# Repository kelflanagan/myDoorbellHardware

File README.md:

# myDoorbell
Software, Schematics, PCB designs, and other material for the myDoorbell project

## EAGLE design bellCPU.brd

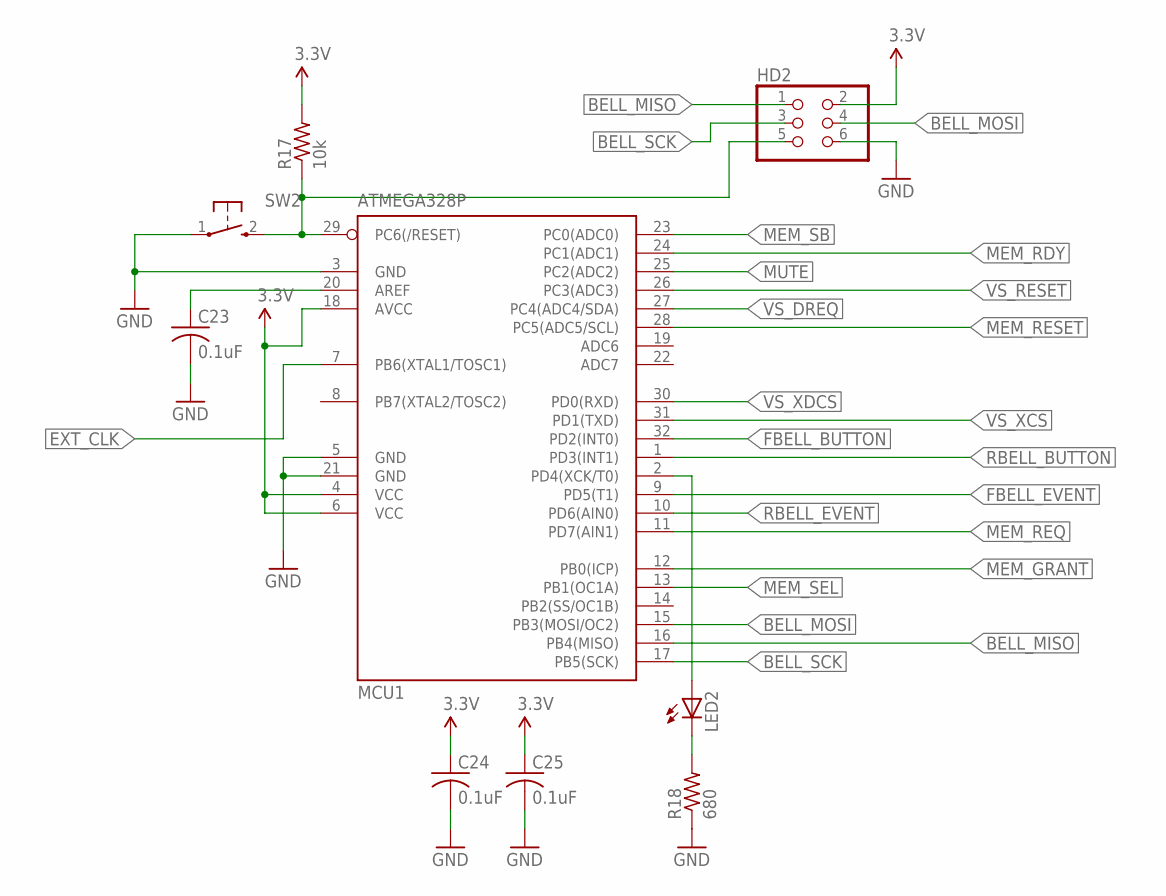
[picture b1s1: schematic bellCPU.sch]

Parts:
C23, C24, C25: 0.1uF; 0603_CAP; DIGIKEY# 399-1096-1-ND
HD2: HEADER_2X3
LED2: LED0603; 0603_LED
MCU1: ATMEGA328P; TQFP32-08
R17: 10k; 0603_RESISTOR; DIGIKEY# P10KGCT-ND
R18: 680; 0603_RESISTOR; DIGIKEY# P680GCT-ND
SW2: SWITCH; SWITCH_TAC

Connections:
3.3V: C24.1, C25.1, HD2.2, MCU1.4 (VCC), MCU1.6 (VCC), MCU1.18 (AVCC), R17.2
BELL_MISO: HD2.1, MCU1.16 (PB4(MISO))
BELL_MOSI: HD2.4, MCU1.15 (PB3(MOSI/OC2))
BELL_RESET: HD2.5, MCU1.29 (PC6(/RESET)), R17.1, SW2.2
BELL_SCK: HD2.3, MCU1.17 (PB5(SCK))
EXT_CLK: MCU1.7 (PB6(XTAL1/TOSC1))
FBELL_BUTTON: MCU1.32 (PD2(INT0))
FBELL_EVENT: MCU1.9 (PD5(T1))
GND: C23.2, C24.2, C25.2, HD2.6, MCU1.3 (GND), MCU1.5 (GND), MCU1.21 (GND), R18.1, SW2.1
MEM_GRANT: MCU1.12 (PB0(ICP))
MEM_RDY: MCU1.24 (PC1(ADC1))
MEM_REQ: MCU1.11 (PD7(AIN1))
MEM_RESET: MCU1.28 (PC5(ADC5/SCL))
MEM_SB: MCU1.23 (PC0(ADC0))
MEM_SEL: MCU1.13 (PB1(OC1A))
MUTE: MCU1.25 (PC2(ADC2))
unnamed: C23.1, MCU1.20 (AREF)
unnamed: LED2.C, R18.2
unnamed: LED2.A, MCU1.2 (PD4(XCK/T0))
RBELL_BUTTON: MCU1.1 (PD3(INT1))
RBELL_EVENT: MCU1.10 (PD6(AIN0))
VS_DREQ: MCU1.27 (PC4(ADC4/SDA))
VS_RESET: MCU1.26 (PC3(ADC3))
VS_XCS: MCU1.31 (PD1(TXD))
VS_XDCS: MCU1.30 (PD0(RXD))

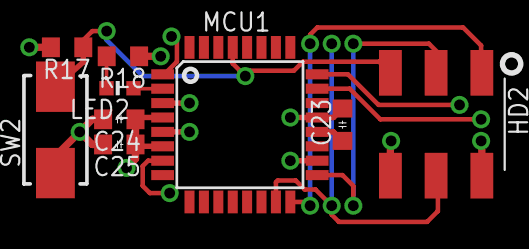
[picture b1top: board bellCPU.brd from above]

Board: 4 copper layers, 9 parts (0 on the bottom side), 9 nets.

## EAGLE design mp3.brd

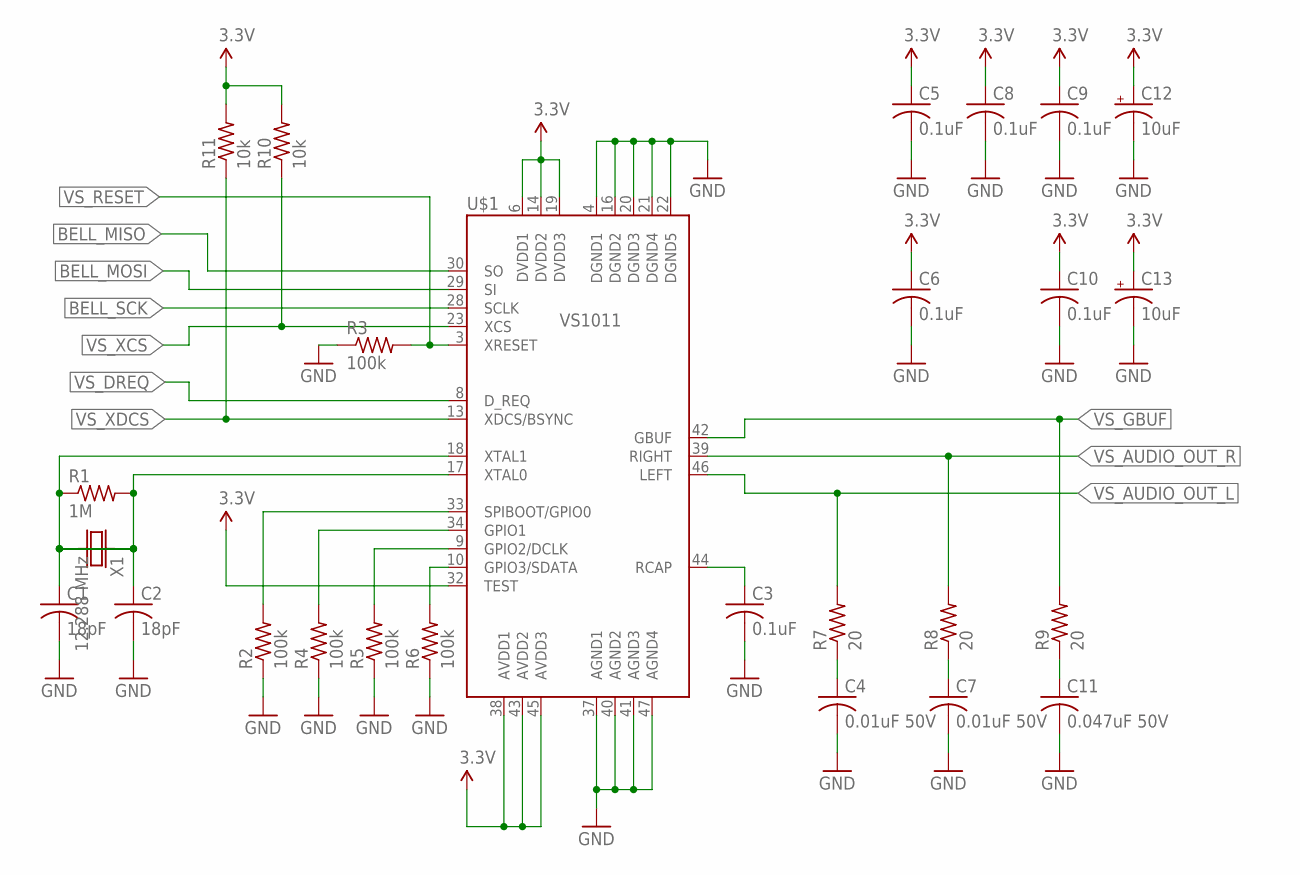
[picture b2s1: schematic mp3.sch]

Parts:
C1, C2: 18pF; 0603_CAP; DIGIKEY# 445-1272-1-ND
C3, C5, C6, C8, C9, C10: 0.1uF; 0603_CAP; DIGIKEY# 399-1096-1-ND
C4, C7: 0.01uF 50V; 0603_CAP; DIGIKEY# 445-1311-1-ND
C11: 0.047uF 50V; 0603_CAP; DIGIKEY# 445-1313-1-ND
C12, C13: 10uF; B_CAP; DIGIKEY# PCE3782CT-ND
R1: 1M; 0603_RESISTOR; DIGIKEY# 311-1.0MGRCT-ND
R2, R3, R4, R5, R6: 100k; 0603_RESISTOR; DIGIKEY# 311-100KGRCT-ND
R7, R8, R9: 20; 0603_RESISTOR; DIGIKEY# 311-20GRCT-ND
R10, R11: 10k; 0603_RESISTOR; DIGIKEY# 311-100KGRCT-ND
U$1: VS1011; LQFP-48
X1: 12.288 MHz; CRYSTAL_5X3; DIGIKEY# 887-1082-1-ND

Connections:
3.3V: C5.1, C6.1, C8.1, C9.1, C10.1, C12.+, C13.+, R10.2, R11.2, U$1.6 (DVDD1), U$1.14 (DVDD2), U$1.19 (DVDD3), U$1.32 (TEST), U$1.38 (AVDD1), U$1.43 (AVDD2), U$1.45 (AVDD3)
BELL_MISO: U$1.30 (SO)
BELL_MOSI: U$1.29 (SI)
BELL_SCK: U$1.28 (SCLK)
GND: C1.2, C2.2, C3.2, C4.2, C5.2, C6.2, C7.2, C8.2, C9.2, C10.2, C11.2, C12.-, C13.-, R2.1, R3.1, R4.1, R5.1, R6.1, U$1.4 (DGND1), U$1.16 (DGND2), U$1.20 (DGND3), U$1.21 (DGND4), U$1.22 (DGND5), U$1.37 (AGND1), U$1.40 (AGND2), U$1.41 (AGND3), U$1.47 (AGND4)
unnamed: C1.1, R1.1, U$1.18 (XTAL1), X1.1
unnamed: C2.1, R1.2, U$1.17 (XTAL0), X1.2
unnamed: C3.1, U$1.44 (RCAP)
unnamed: R6.2, U$1.10 (GPIO3/SDATA)
unnamed: R5.2, U$1.9 (GPIO2/DCLK)
unnamed: R4.2, U$1.34 (GPIO1)
unnamed: R2.2, U$1.33 (SPIBOOT/GPIO0)
unnamed: C4.1, R7.1
unnamed: C7.1, R8.1
unnamed: C11.1, R9.1
VS_AUDIO_OUT_L: R7.2, U$1.46 (LEFT)
VS_AUDIO_OUT_R: R8.2, U$1.39 (RIGHT)
VS_DREQ: U$1.8 (D_REQ)
VS_GBUF: R9.2, U$1.42 (GBUF)
VS_RESET: R3.2, U$1.3 (XRESET)
VS_XCS: R10.1, U$1.23 (XCS)
VS_XDCS: R11.1, U$1.13 (XDCS/BSYNC)

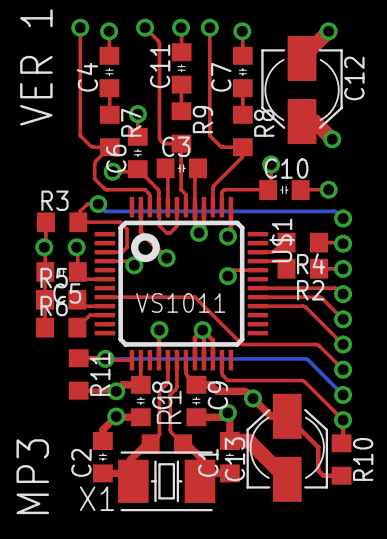
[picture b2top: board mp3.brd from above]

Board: 4 copper layers, 26 parts (0 on the bottom side), 18 nets.

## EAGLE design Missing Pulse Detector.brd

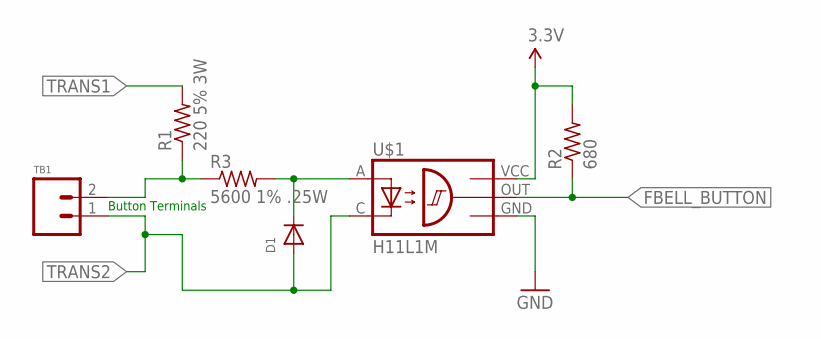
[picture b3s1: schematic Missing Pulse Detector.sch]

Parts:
D1: DIODE0603; 0603_DIODE; DIGIKEY# 641-1002-1-ND
R1: 220 5% 3W; 4122_RESISTOR; DIGIKEY# A103620CT-ND
R2: 680; 0603_RESISTOR; DIGIKEY# P680GCT-ND
R3: 5600 1% .25W; 1206_RESISTOR; DIGIKEY# P5.60KFCT-ND
TB1: TERMINAL_BLOCK_2
U$1: H11L1M; SOIC6

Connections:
3.3V: R2.2, U$1.VCC
FBELL_BUTTON: R2.1, U$1.OUT
FDB1: R1.1, R3.1, TB1.2
GND: U$1.GND
unnamed: D1.C, R3.2, U$1.A
TRANS1: R1.2
TRANS2: D1.A, TB1.1, U$1.C

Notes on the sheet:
Button Terminals

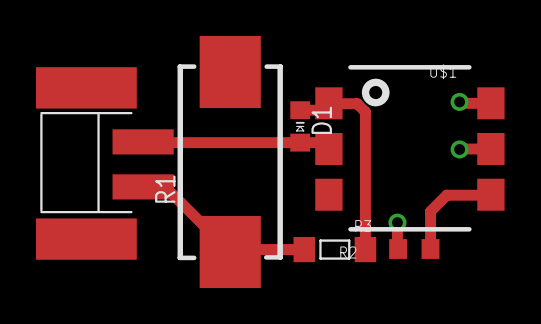
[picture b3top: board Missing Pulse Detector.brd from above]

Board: 4 copper layers, 6 parts (0 on the bottom side), 5 nets.

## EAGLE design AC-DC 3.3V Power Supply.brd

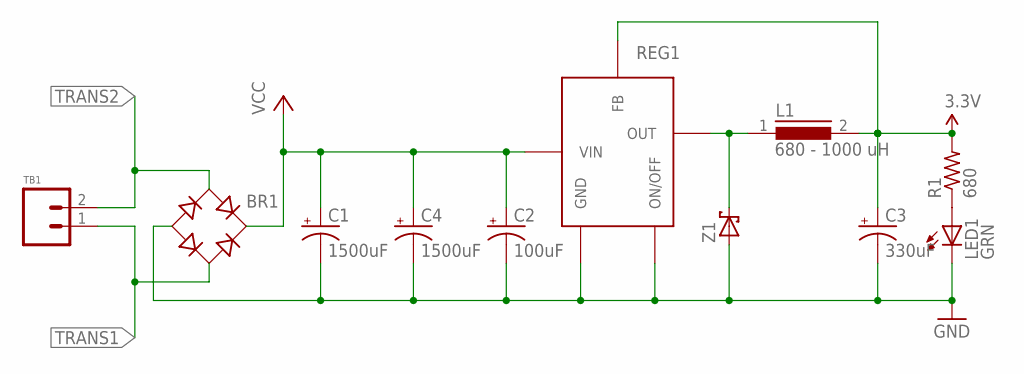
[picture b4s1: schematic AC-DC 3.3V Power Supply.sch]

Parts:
BR1: BR; DFS
C1, C4: 1500uF; J16_CAP; DIGIKEY# PCE3466CT-ND
C2: 100uF; F_CAP; DIGIKEY# PCE3917CT-ND
C3: 330uF; F_CAP; DIGIKEY# PCE3401CT-ND
L1: 680 - 1000 uH; DR125; DIGIKEY# SRR1208-102KLCT-ND
LED1: GRN; 0603_LED
R1: 680; 0603_RESISTOR; DIGIKEY# P680GCT-ND
REG1: TL2575; TO-263-6
TB1: TERMINAL_BLOCK_2
Z1: SCHOTTKY_DIODE; SMD_DIODE

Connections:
3.3V: C3.+, L1.2, R1.2, REG1.4 (FB)
GND: BR1.-, C1.-, C2.-, C3.-, C4.-, LED1.C, REG1.3 (GND), REG1.5 (ON/OFF), Z1.A
unnamed: LED1.A, R1.1
unnamed: L1.1, REG1.2 (OUT), Z1.C
TRANS1: BR1.AC2, TB1.1
TRANS2: BR1.AC1, TB1.2
VCC: BR1.+, C1.+, C2.+, C4.+, REG1.1 (VIN)

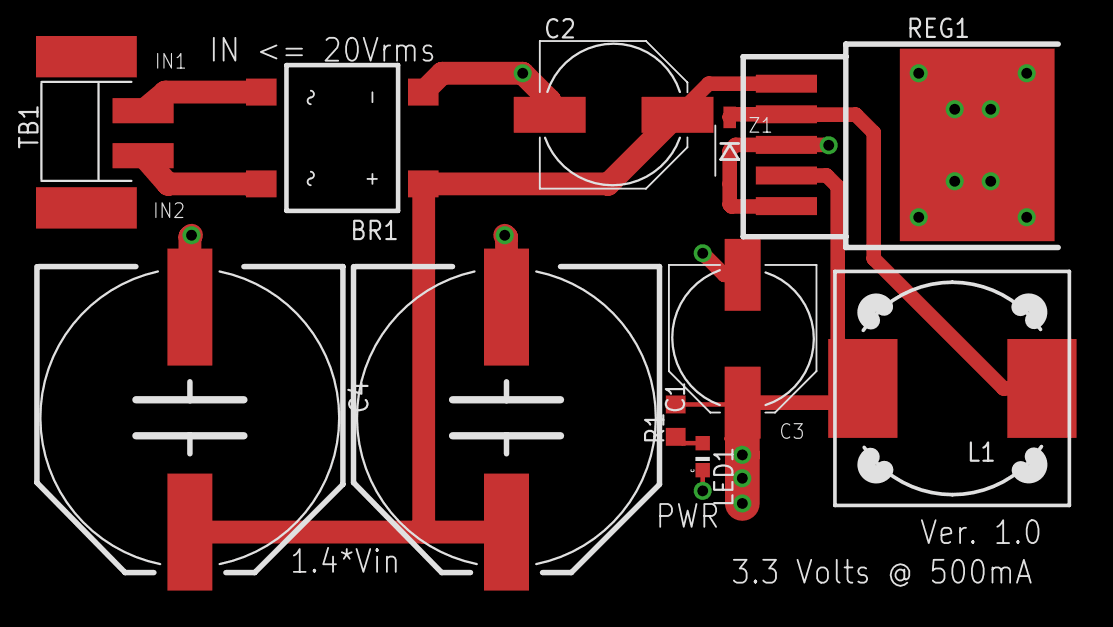
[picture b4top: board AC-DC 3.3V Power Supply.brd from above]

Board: 2 copper layers, 11 parts (0 on the bottom side), 7 nets.

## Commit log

2016-03-30 Eagle file for 16 V AC to 3.3 V DC Power Supply
2016-03-30 Eagle PCB file for 16 V AC to 3.3 VDC Power Supply
2016-03-30 Bill of Material
2016-04-06 Eagle file for doorbell detection circuit
    This schematic describes a circuit for detecting a doorbell close event from a standard doorbell circuit and generates an output suitable for use by a microcontroller.
2016-04-06 Eagle PCB file for missing pulse detector
2016-04-06 Gerber Files for PCB
2016-04-12 CPU and MP3 modules

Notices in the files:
parts and their libraries:
SparkFun-Aesthetics: Licensing: CC v3.0 Share-Alike You are welcome to use this library for commercial purposes.
